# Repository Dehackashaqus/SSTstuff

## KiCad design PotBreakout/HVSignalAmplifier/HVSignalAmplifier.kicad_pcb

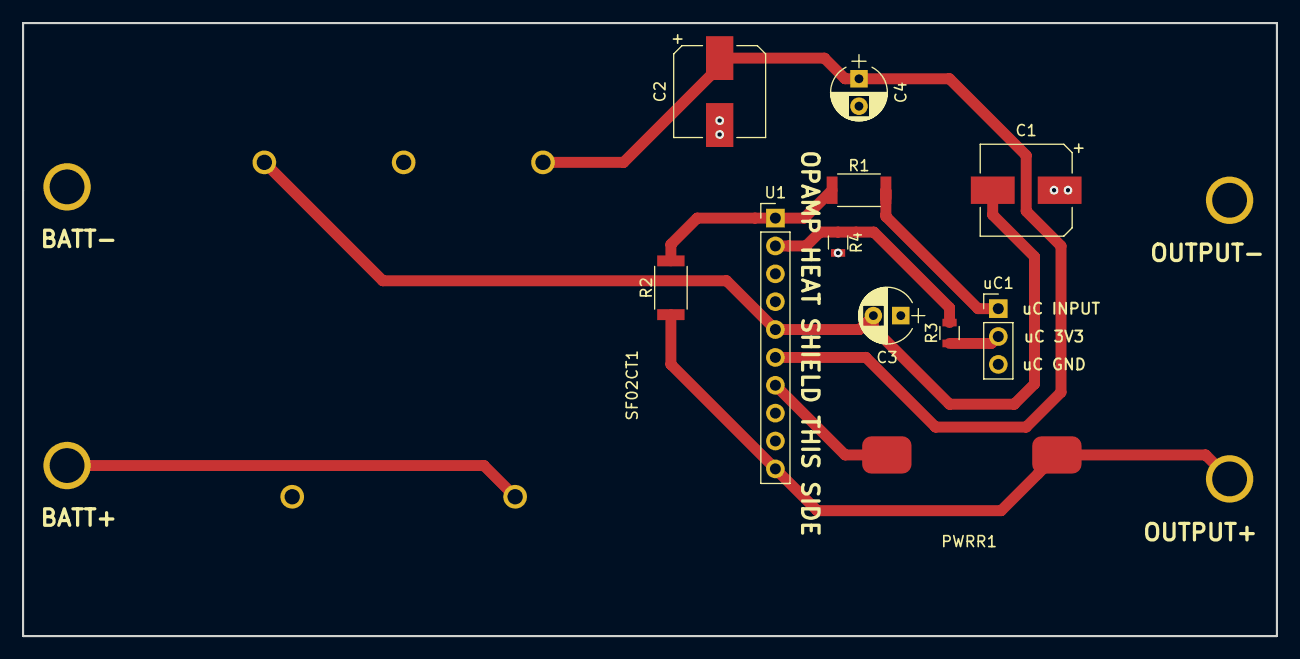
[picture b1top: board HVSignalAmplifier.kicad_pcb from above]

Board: 2 copper layers, 114.3 x 55.9 mm, 14 parts (0 on the bottom side), 10 nets.

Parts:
BATTERY1: Conn_01x02_Female; 2PINHV
C1, C2: 10uF; CP_Elec_8x6.5
C3, C4: 100nF; CP_Radial_D5.0mm_P2.50mm
OUTPUT+: Conn_01x02_Female; 2PINHV
PWRR1: 3 OHM; PWRRES
R1: 1k; R_2010
R2: 48.5k; R_2010
R3, R4: 1k; R_0805
SF02CT1: Conn_01x05_Female; SF02
U1: PA15FL; PinHeader_1x10_P2.54mm_Vertical
uC1: Conn_01x03_Female; PinHeader_1x03_P2.54mm_Vertical

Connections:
+IN: BATTERY1.1, SF02CT1.1
+SUPPLY: C2.1, C4.1, SF02CT1.3, U1.6
-SUPPLY: C1.2, C3.2, SF02CT1.4, U1.5
GND: BATTERY1.2, C1.1, C2.2, C3.1, C4.2, OUTPUT+.2, R4.2, SF02CT1.2, SF02CT1.5, uC1.3
unnamed: PWRR1.1, U1.7
unnamed: R1.1, R2.2, U1.1
unnamed: R3.2, R4.1, U1.2
OUT: OUTPUT+.1, PWRR1.2, R2.1, U1.10
uC_3V3: R3.1, uC1.2
uC_IN: R1.2, uC1.1

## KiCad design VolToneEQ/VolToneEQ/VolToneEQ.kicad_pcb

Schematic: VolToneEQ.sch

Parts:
3WaySwitch1: Conn_01x04; Pin_Header_Straight_1x04_Pitch2.54mm
4pdt1: Conn_02x06_Counter_Clockwise; 4pdtFP
6pdt1, 6pdt2: Conn_02x09_Odd_Even; 6pdtFP
9V1: Battery; 9vholder
BASS1: 100k; Potentiometer_Bourns_PTV09A-1_Single_Vertical
BridgeTonePot1: Conn_02x07_Odd_Even; Pin_Header_Straight_2x07_Pitch2.54mm
BridgeVolPot1: Conn_02x07_Odd_Even; Pin_Header_Straight_2x07_Pitch2.54mm
C1, C17: 22n; C_1206_3216Metric_Pad1.42x1.75mm_HandSolder
C2, C6: 47p; C_Rect_L7.2mm_W4.5mm_P5.00mm_FKS2_FKP2_MKS2_MKP2
C3: 10n; C_1206_3216Metric_Pad1.42x1.75mm_HandSolder
C4: 1n; C_0805_2012Metric_Pad1.15x1.40mm_HandSolder
C5: 100n; C_1210_3225Metric_Pad1.42x2.65mm_HandSolder
C7: 47n; C_1206_3216Metric_Pad1.42x1.75mm_HandSolder
C8, C25, C26: 470p; C_0805_2012Metric_Pad1.15x1.40mm_HandSolder
C10: 100u; CP_Radial_D8.0mm_P5.00mm
C11, C15, C20: 100n; C_1206_3216Metric_Pad1.42x1.75mm_HandSolder
C12: 220p; C_0805_2012Metric_Pad1.15x1.40mm_HandSolder
C13, C22: 10n; C_0805_2012Metric_Pad1.15x1.40mm_HandSolder
C14, C19: 22u; CP_Radial_D5.0mm_P2.00mm
C16: 4.7n; C_1206_3216Metric_Pad1.42x1.75mm_HandSolder
C18, C23: 220n; C_2816_7142Metric_Pad3.20x4.45mm_HandSolder
C21: 2.2n; C_0805_2012Metric_Pad1.15x1.40mm_HandSolder
C24, C27: .022u; C_1206_3216Metric_Pad1.42x1.75mm_HandSolder
D1, D2, D4, D5: LED; LED_D3.0mm
D3: D; LED_D3.0mm
GROUNDBRIDGE1: Conn_01x01; Pin_Header_Straight_1x01_Pitch2.54mm
Jack1: Conn_01x03; Pin_Header_Straight_1x03_Pitch2.54mm
NeckTonePot1: Conn_02x07_Odd_Even; Pin_Header_Straight_2x07_Pitch2.54mm
NeckVolumePot1: Conn_02x07_Odd_Even; Pin_Header_Straight_2x07_Pitch2.54mm
PickupInputs1: Conn_01x10; Pin_Header_Straight_1x10_Pitch2.54mm
Q1, Q2: ZTX951; TO-92_Inline_Narrow_Oval
R1: 1MEG; R_0805_2012Metric_Pad1.15x1.40mm_HandSolder
R2, R29: 470k; R_0805_2012Metric_Pad1.15x1.40mm_HandSolder
R3, R8, R17, R18, R35: 10k; R_0805_2012Metric_Pad1.15x1.40mm_HandSolder
R4, R12: 330k; R_0805_2012Metric_Pad1.15x1.40mm_HandSolder
R5, R9, R10, R13, R14, R21, R25, R32: 22k; R_0805_2012Metric_Pad1.15x1.40mm_HandSolder
R6, R11: 250k; R_0805_2012Metric_Pad1.15x1.40mm_HandSolder
R7: 4.7k; R_0805_2012Metric_Pad1.15x1.40mm_HandSolder
R15: 39k; R_0805_2012Metric_Pad1.15x1.40mm_HandSolder
R16: 10; R_0805_2012Metric_Pad1.15x1.40mm_HandSolder
R19, R22, R27, R28, R30, R31: 2.2k; R_0805_2012Metric_Pad1.15x1.40mm_HandSolder
R20, R24: 20k; R_0805_2012Metric_Pad1.15x1.40mm_HandSolder
R23, R26: 33k; R_0805_2012Metric_Pad1.15x1.40mm_HandSolder
R33: 100k; R_0805_2012Metric_Pad1.15x1.40mm_HandSolder
R34: 3.3K; R_0805_2012Metric_Pad1.15x1.40mm_HandSolder
RANGE1: 100k; Potentiometer_Bourns_3386P_Vertical
TIGHT1: 100kREV; Potentiometer_Bourns_PTV09A-1_Single_Vertical
TRANGAIN1: 250k; Potentiometer_Bourns_3386P_Vertical
TRBLD1: Conn_02x02_Top_Bottom; TrebBldDIP
TREBLE1: 100k; Potentiometer_Bourns_PTV09A-1_Single_Vertical
U1, U2, U3, U4: TL072; SOIC-8_3.9x4.9mm_Pitch1.27mm
VOL1: 50k; Potentiometer_Bourns_PTV09A-1_Single_Vertical

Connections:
BRBLACK: BridgeTonePot1.8, PickupInputs1.2
BRGRN: 4pdt1.3, 4pdt1.12, PickupInputs1.4
BRGRN2: 3WaySwitch1.1, 4pdt1.11, 6pdt2.1, BASS1.1, BASS1.2, BridgeTonePot1.7, BridgeTonePot1.13, BridgeVolPot1.1, BridgeVolPot1.4, BridgeVolPot1.9, BridgeVolPot1.13, C2.2, C4.2, C5.2, C10.2, C11.2, C13.2, C14.2, C15.2, C16.2, C19.2, C20.2, C22.2, C24.2, C27.2, GROUNDBRIDGE1.1, Jack1.3, NeckTonePot1.13, NeckVolumePot1.13, PickupInputs1.5, PickupInputs1.10, R1.2, R21.2, R25.2, R33.2, U1.4 (V-), U2.4 (V-), U3.4 (V-), U4.4 (V-)
BROUT: 3WaySwitch1.4, BridgeVolPot1.11
BRRED: 4pdt1.1, 4pdt1.10, PickupInputs1.1
BRRED2: 4pdt1.2, 6pdt1.4, 6pdt1.13, NeckTonePot1.8
BRTONECAPIN: 6pdt2.7, C24.1
BRTONEGANG1IN: 6pdt2.10, BridgeTonePot1.6
BRTONEGANG1OUT: 6pdt1.17, 6pdt2.9, BridgeTonePot1.4
BRTONEGANG2IN: 6pdt2.11, BridgeTonePot1.3
BRWHT: BridgeTonePot1.11, PickupInputs1.3
BTONEIN: 6pdt1.15, BridgeTonePot1.5
BVINTRAD: 6pdt1.2, BridgeVolPot1.6, TRBLD1.2
BVOUT: 6pdt1.3, BridgeVolPot1.7, BridgeVolPot1.12
BVOUTTRAD: 6pdt1.1, BridgeVolPot1.5, C25.2, R4.2
FinalOut: 6pdt2.4, Jack1.2
GAINPOTOUT: BridgeTonePot1.1, BridgeTonePot1.2, D1.1, D2.2, R10.2
GAINSTAGEPOTIN: 6pdt2.12, C6.1, C7.2, D1.2, D2.1, U1.7
MASTEROUT: BridgeVolPot1.2, C1.2, R1.1
NBLACK: NeckTonePot1.11, PickupInputs1.7, PickupInputs1.8
NGRN: 4pdt1.4, 4pdt1.9, PickupInputs1.6, PickupInputs1.9
NGRN2: 4pdt1.8, NeckVolumePot1.11
NOUT: 3WaySwitch1.2, 6pdt1.9, BridgeVolPot1.10
NRED2: 4pdt1.5, NeckVolumePot1.8
NTONE: 6pdt1.10, 6pdt1.16, NeckVolumePot1.9, NeckVolumePot1.10
NTONEIN: 6pdt1.14, NeckTonePot1.5
NVINTRAD: 6pdt1.8, C26.1, NeckVolumePot1.6, R12.1
NVOUTTRAD: 6pdt1.7, NeckVolumePot1.5, TRBLD1.4
unnamed: 4pdt1.6, 4pdt1.7
unnamed: 6pdt1.5, 6pdt1.6
unnamed: 6pdt1.11, 6pdt1.12
unnamed: 9V1.1, D3.2
unnamed: BASS1.3, C18.2
unnamed: BridgeTonePot1.10, NeckTonePot1.9
unnamed: BridgeTonePot1.9, BridgeTonePot1.12
unnamed: BridgeVolPot1.8, NeckTonePot1.10, NeckVolumePot1.4, NeckVolumePot1.7, NeckVolumePot1.12
unnamed: C1.1, R2.2, R3.2
unnamed: C2.1, R3.1, U1.3 (+)
unnamed: C3.1, R7.1, R8.2
unnamed: C3.2, R15.1, U1.1
unnamed: C4.1, R8.1, U1.5 (+)
unnamed: C5.1, R9.2
unnamed: C6.2, R9.1, R10.1, U1.6 (-)
unnamed: C7.1, R13.2
unnamed: C8.1, Q1.1, Q2.3, R17.2, TRANGAIN1.1, TRANGAIN1.2, U2.1
unnamed: C8.2, Q1.3, Q2.1, R14.2
unnamed: C10.1, C11.1, R16.1, R20.1, R24.1, U1.8 (V+), U2.8 (V+), U3.8 (V+), U4.8 (V+)
unnamed: C12.2, R18.2, RANGE1.1
unnamed: C13.1, D4.1, D5.2, R19.1, TREBLE1.3
unnamed: C14.1, C15.1, R20.2, R21.1, R22.2
unnamed: C16.1, TREBLE1.1
unnamed: C17.1, R26.1, R27.2, U3.1
unnamed: C17.2, R23.2, U3.2 (-)
unnamed: C18.1, R23.1, R26.2
unnamed: C19.1, C20.1, R24.2, R25.1, R28.2
unnamed: C21.2, R31.1, U3.6 (-)
unnamed: C22.1, R32.2
unnamed: C23.1, R33.1, R34.2
unnamed: C25.1, R4.1, TRBLD1.1
unnamed: C26.2, R12.2, TRBLD1.3
unnamed: C27.1, NeckTonePot1.4
unnamed: D3.1, R16.2
unnamed: R7.2, TIGHT1.3
unnamed: R13.1, R14.1, TRANGAIN1.3, U2.2 (-)
unnamed: R5.1, R15.2, U1.2 (-)
unnamed: R17.1, R18.1, U2.6 (-)
unnamed: R22.1, U4.3 (+)
unnamed: R27.1, VOL1.3
unnamed: R28.1, U4.5 (+)
unnamed: R29.1, R30.1, VOL1.2
unnamed: R30.2, U3.5 (+)
unnamed: TREBLE1.2, U3.3 (+)
ODMIDGND: NeckVolumePot1.1, R6.2, R11.1, R32.1
ODMIDIN: C21.1, C23.2, NeckVolumePot1.3, R6.1, R11.2, U3.7
ODMIDOUT: NeckVolumePot1.2, R31.2
ODin: 6pdt2.3, BridgeVolPot1.3
ODout: 6pdt2.6, R34.1
OUT: 3WaySwitch1.3, 6pdt2.2, 6pdt2.5
PRESIN: C12.1, NeckTonePot1.1, R35.1, RANGE1.2, RANGE1.3, U2.7
PRESOUT: NeckTonePot1.2, NeckTonePot1.3, R19.2, R35.2
PWRGND: 9V1.2, Jack1.1
Vref: R2.1, R5.2, TIGHT1.1, TIGHT1.2, U4.1, U4.2 (-)
Vref2: D4.2, D5.1, R29.2, U2.3 (+), U2.5 (+), U4.6 (-), U4.7, VOL1.1

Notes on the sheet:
7,8,9 S1B (LEFT SIDE) 10,11,12 S1A
WIMA .022u 5mm
7,8,9 S4A (LEFT SIDE) 10,11,12 S4B
7,8,9 S3B (LEFT SIDE) 10,11,12 S3A
7,8,9 S2A (LEFT SIDE) 10,11,12 S2B
These 2 switches control traditional vs 3 band EQ selection
Tip
Sleeve
Ring

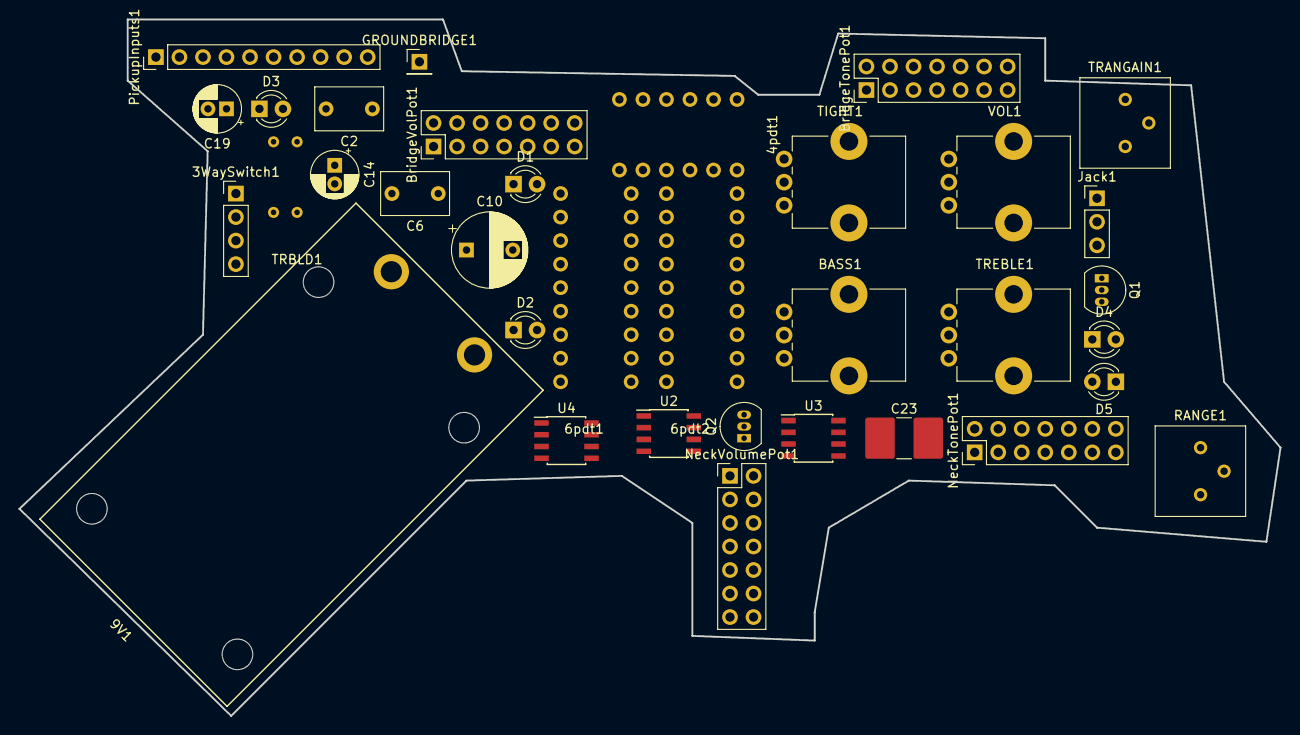
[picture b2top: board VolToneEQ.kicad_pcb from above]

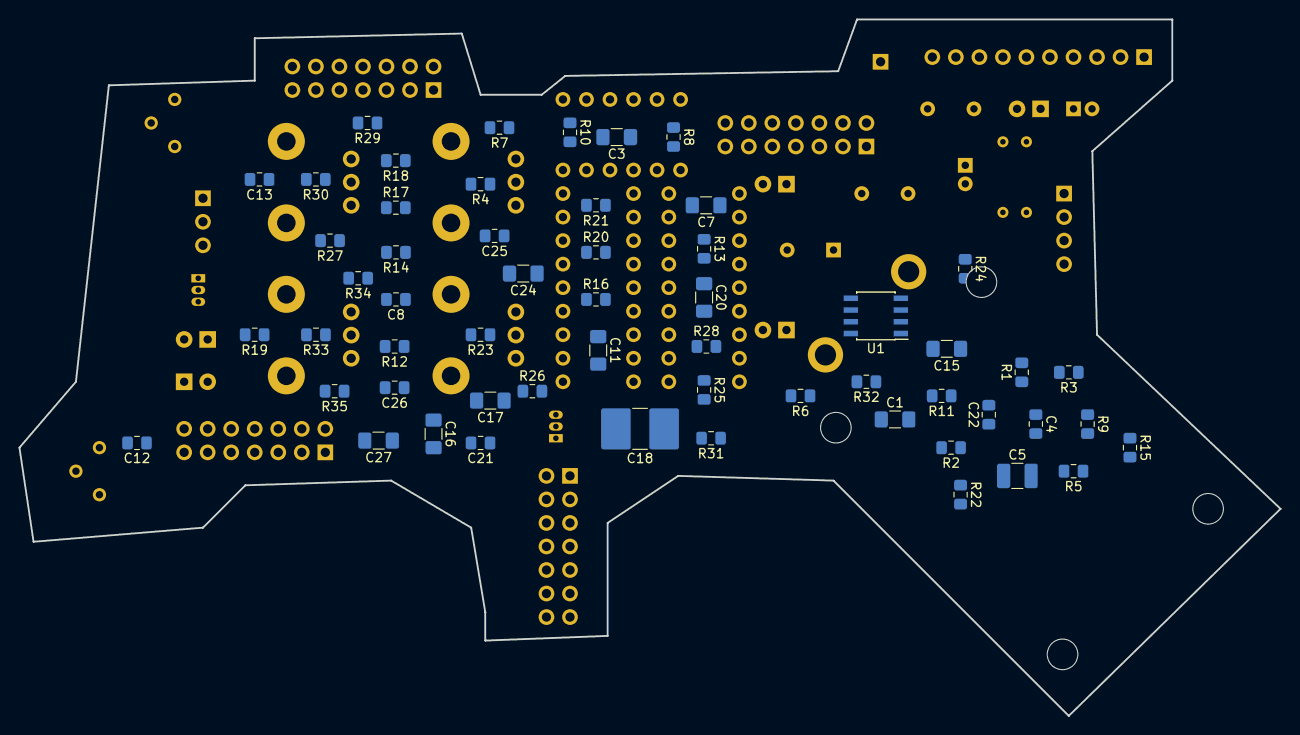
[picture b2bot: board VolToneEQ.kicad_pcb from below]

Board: 2 copper layers, 136.1 x 75.2 mm, 91 parts (56 on the bottom side), 83 nets, no tracks yet.

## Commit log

2018-08-20 Breakout for Bourns GTR 183 Dual Gang (14 pin)
2018-08-23 Finalized pot breakout board
2018-08-23 Started main pcb
2018-08-30 Added most connections
    Still needs EQ circuit and enough switches to cuf off both tone pots. might have to use 2 4pdts. Also make initial phase switches into one 4pdt.
2018-08-30 Updated LTSpice schematic with EQ
2018-09-03 Started work on overdrive circuit. May removed 3 band eq.
2018-09-04 Added hard clipping and input buffer
2018-09-06 updated tube screamer to crunch box
2018-09-10 Added parallel resistors to account for 500k pots, added soft clipping
2018-09-13 can't remember what i did
2018-09-13 started updating eeschema
2018-09-17 changed to BE OD
2018-09-20 changed to be od with mid
2018-09-21 fixed be od and changed second clipping to pnp
2018-09-21 Finished OD circuit
2018-09-24 started adding footprints
2018-09-25 Started laying out board
2018-09-25 Organized Layout
2018-09-28 routed board
2018-09-28 fixed one error with overlap
2018-10-01 added 100k parallel to volume
2018-10-01 improved some traces
2018-10-01 altered pot breakout
2018-10-02 changed potbreakout and widened traces
2018-10-02 finalized and ordered all boards
2018-10-11 fucked it up. gotta redo
2018-10-19 revised layout to fit
2019-02-21 Added Dr Board
2019-02-21 Finalized Dist Circuit
2019-05-24 moved HV stuff to new directory
